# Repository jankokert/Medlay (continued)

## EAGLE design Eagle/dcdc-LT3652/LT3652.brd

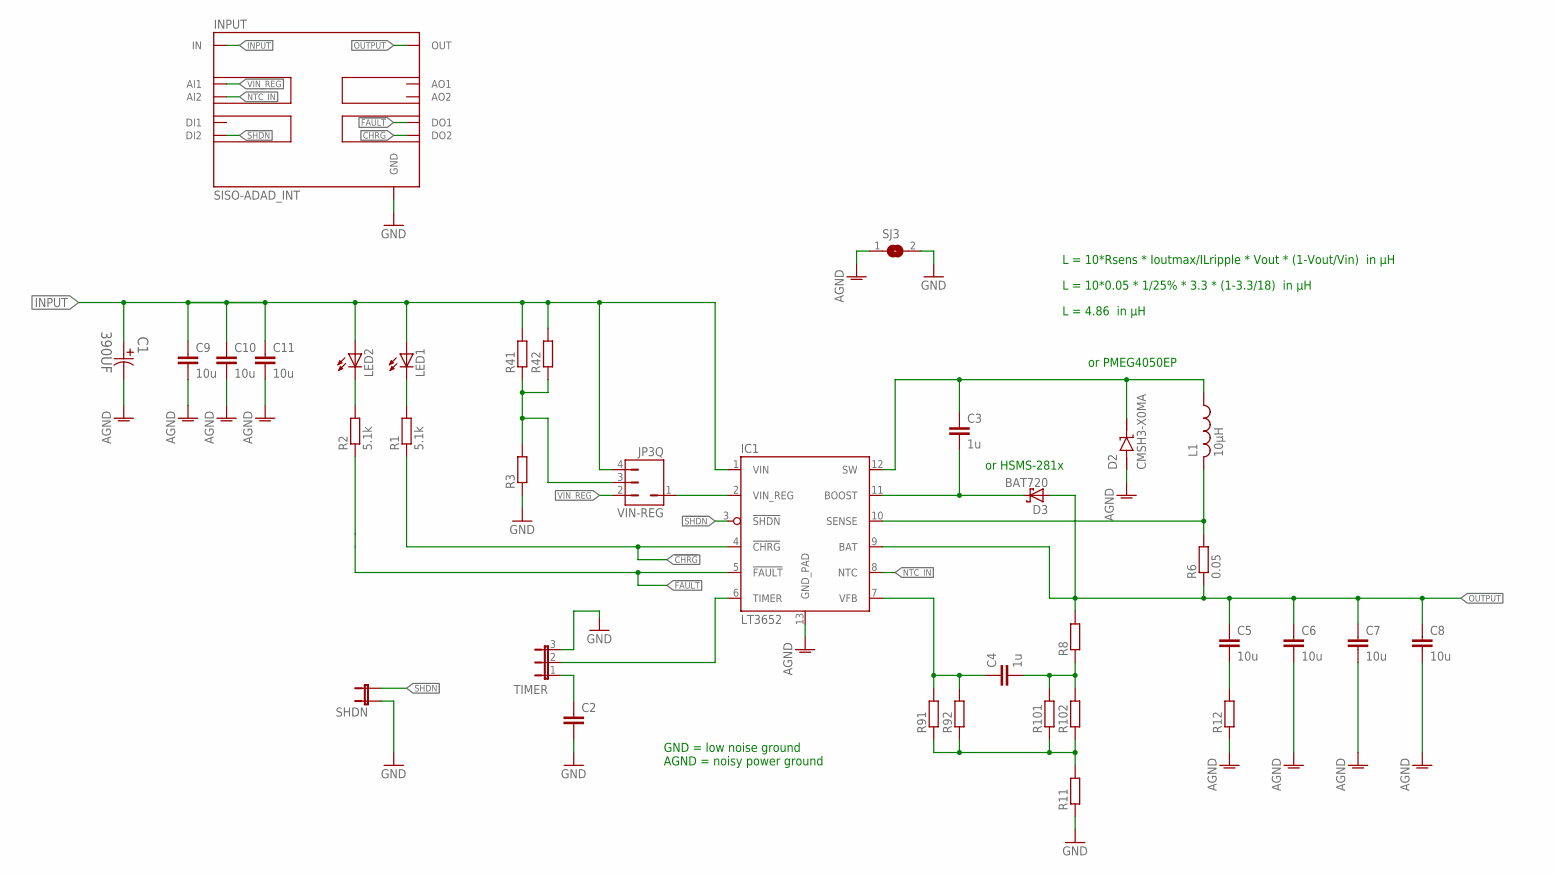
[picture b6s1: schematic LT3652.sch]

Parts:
C1: 390UF; CAPAE1030X1050N
C2: C-EUC0805; C0805
C3, C4: 1u; C0805
C5, C6, C7, C8, C9, C10, C11: 10u; C0805
D2: CMSH3-X0MA; DIODE_SMA
D3: BAT720; SOT23
IC1: LT3652; MSOP-12_GND
INPUT: SISO-ADAD_INT; SISO-ADAD
L1: 10µH; 2525
LED1, LED2: LEDCHIP-LED0805; CHIP-LED0805
R1, R2: 5.1k; R0805
R3, R8, R11, R12, R41, R42, R91, R92, R101, R102: R-EU_R0805; R0805
R6: 0.05; R1206
SHDN: JP2_SMALL_PAD
SJ3: SJ2
TIMER: JP3_SMALL_PAD
VIN-REG: JP3Q; JP1-3

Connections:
!CHRG: IC1.4 (!CHRG), INPUT.DO2, R1.1
!FAULT: IC1.5 (!FAULT), INPUT.DO1, R2.1
!SHDN: IC1.3 (!SHDN), INPUT.DI2, SHDN.2
AGND: C1.2, C6.2, C7.2, C8.2, C9.2, C10.2, C11.2, D2.A, IC1.13 (GND_PAD), R12.1, SJ3.1
D1: LED2.C, R2.2
GND: C2.2, INPUT.GND1 (GND), INPUT.GND2 (GND), INPUT.GND3 (GND), INPUT.GND4 (GND), R3.1, R11.1, SHDN.1, SJ3.2, TIMER.3
INPUT: C1.1, C9.1, C10.1, C11.1, IC1.1 (VIN), INPUT.IN1 (IN), INPUT.IN2 (IN), INPUT.IN3 (IN), INPUT.IN4 (IN), LED1.A, LED2.A, R41.2, R42.2, VIN-REG.4
unnamed: IC1.6 (TIMER), TIMER.2
unnamed: LED1.C, R1.2
unnamed: R3.2, R41.1, R42.1, VIN-REG.3
unnamed: IC1.2 (VIN_REG), VIN-REG.1
unnamed: C3.1, D2.C, IC1.12 (SW), L1.P$2
unnamed: C3.2, D3.3 (C), IC1.11 (BOOST)
unnamed: C2.1, TIMER.1
unnamed: R11.2, R91.1, R92.1, R101.1, R102.1
unnamed: C4.2, R8.1, R101.2, R102.2
unnamed: C5.2, R12.2
unnamed: IC1.10 (SENSE), L1.P$1, R6.2
unnamed: C4.1, IC1.7 (VFB), R91.2, R92.2
NTC_IN: IC1.8 (NTC), INPUT.AI2
OUTPUT: C5.1, C6.1, C7.1, C8.1, D3.1 (A), IC1.9 (BAT), INPUT.OUT1_1 (OUT), INPUT.OUT1_2 (OUT), INPUT.OUT1_3 (OUT), INPUT.OUT1_4 (OUT), R6.1, R8.2
VIN_REG: INPUT.AI1, VIN-REG.2

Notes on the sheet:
or HSMS-281x
GND = low noise ground AGND = noisy power ground
L = 10*Rsens * Ioutmax/ILripple * Vout * (1-Vout/Vin) in µH
L = 10*0.05 * 1/25% * 3.3 * (1-3.3/18) in µH
L = 4.86 in µH
or PMEG4050EP

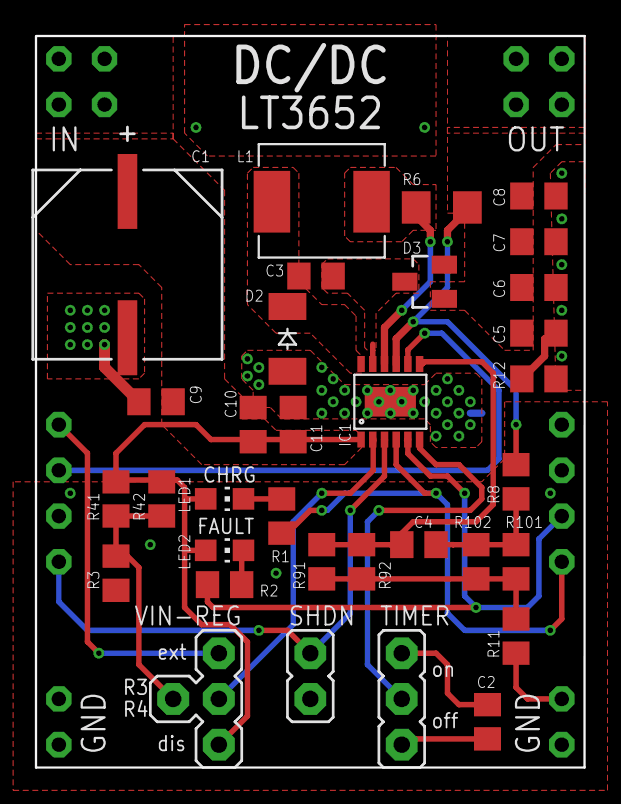
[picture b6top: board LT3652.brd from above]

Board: 2 copper layers, 30.5 x 40.6 mm, 35 parts (1 on the bottom side), 22 nets.

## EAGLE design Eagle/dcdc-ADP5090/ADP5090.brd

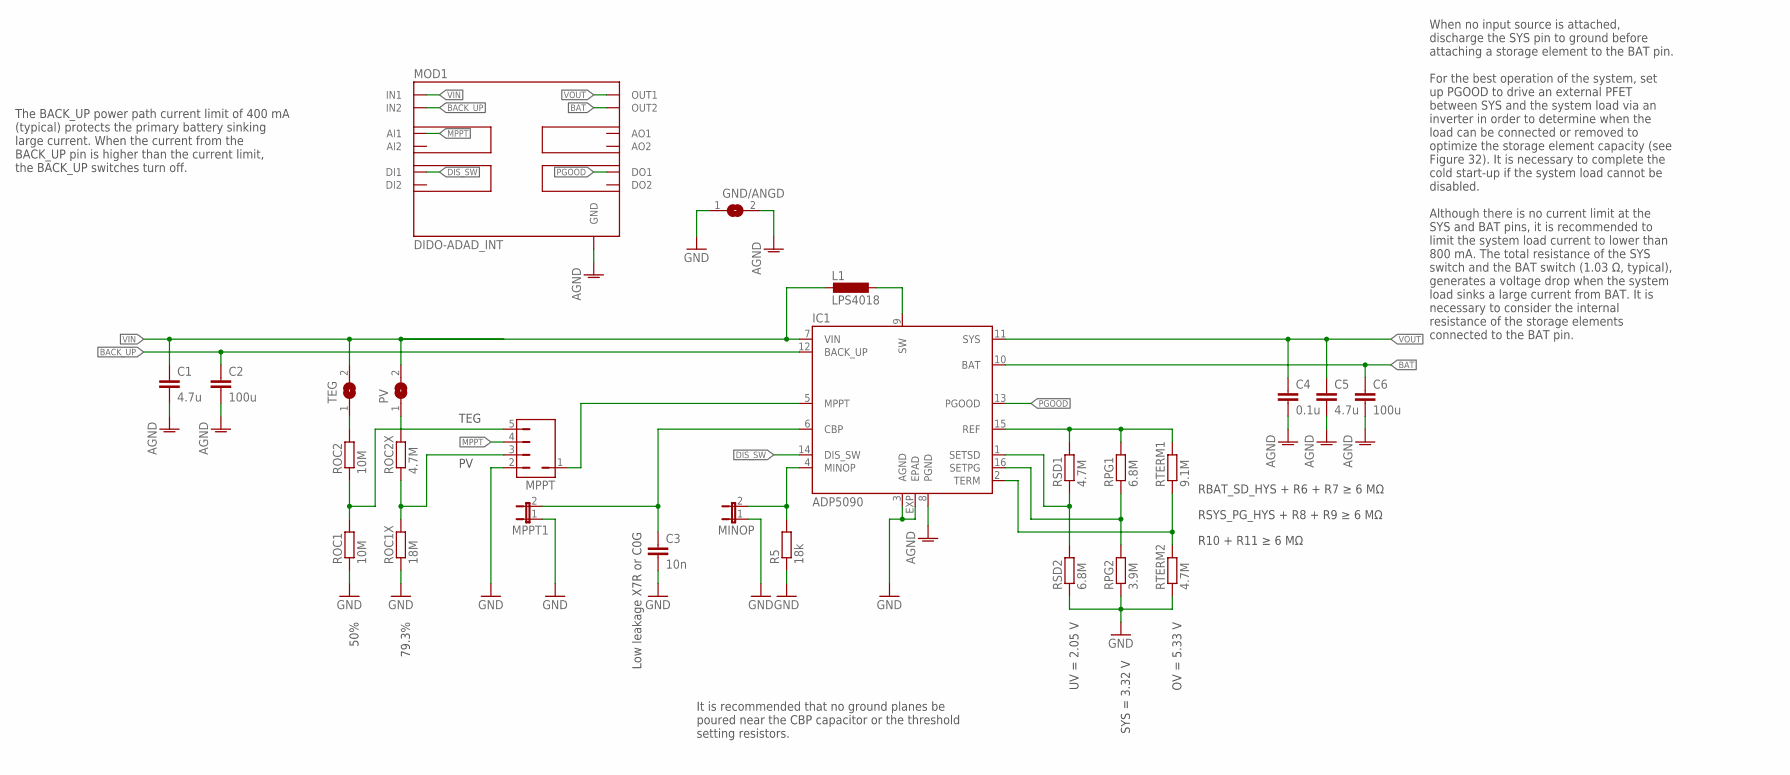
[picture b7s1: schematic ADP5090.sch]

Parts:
C1, C5: 4.7u; C0805
C2, C6: 100u; C0805
C3: 10n; C0805
C4: 0.1u; C0805
GND/ANGD: SJ
IC1: ADP5090; LFCSP16_WQ_CP-16-33
L1: LPS4018
MINOP: JP1E; JP1
MOD1: DIDO-ADAD_INT; DIDO-ADAD
MPPT: JP3Q; JP1-4
MPPT1: JP1E; JP1
PV: SJ
R5: 18k; R0805
ROC1, ROC2: 10M; R0805
ROC1X: 18M; R0805
ROC2X: 4.7M; R0805
RPG1: 6.8M; R0805
RPG2: 3.9M; R0805
RSD1: 4.7M; R0805
RSD2: 6.8M; R0805
RTERM1: 9.1M; R0805
RTERM2: 4.7M; R0805
TEG: SJ

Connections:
AGND: C1.2, C2.2, C4.2, C5.2, C6.2, GND/ANGD.2, IC1.8 (PGND), MOD1.GND1 (GND), MOD1.GND2 (GND), MOD1.GND3 (GND), MOD1.GND4 (GND)
BACK_UP: C2.1, IC1.12 (BACK_UP), MOD1.IN2_1 (IN2), MOD1.IN2_2 (IN2), MOD1.IN2_3 (IN2), MOD1.IN2_4 (IN2)
BAT: C6.1, IC1.10 (BAT), MOD1.OUT2_1 (OUT2), MOD1.OUT2_2 (OUT2), MOD1.OUT2_3 (OUT2), MOD1.OUT2_4 (OUT2)
DIS_SW: IC1.14 (DIS_SW), MOD1.DI1
GND: C3.2, GND/ANGD.1, IC1.3 (AGND), IC1.EXP (EPAD), MINOP.1, MPPT.2, MPPT1.1, R5.1, ROC1.1, ROC1X.1, RPG2.1, RSD2.1, RTERM2.1
MPPT: MOD1.AI1, MPPT.4
unnamed: IC1.15 (REF), RPG1.2, RSD1.2, RTERM1.2
unnamed: IC1.1 (SETSD), RSD1.1, RSD2.2
unnamed: IC1.16 (SETPG), RPG1.1, RPG2.2
unnamed: IC1.2 (TERM), RTERM1.1, RTERM2.2
unnamed: C3.1, IC1.6 (CBP), MPPT1.2
unnamed: MPPT.3, ROC1X.2, ROC2X.1
unnamed: IC1.5 (MPPT), MPPT.1
unnamed: ROC2.2, TEG.1
unnamed: MPPT.5, ROC1.2, ROC2.1
unnamed: PV.1, ROC2X.2
unnamed: IC1.9 (SW), L1.2
unnamed: IC1.4 (MINOP), MINOP.2, R5.2
PGOOD: IC1.13 (PGOOD), MOD1.DO1
VIN: C1.1, IC1.7 (VIN), L1.1, MOD1.IN1_1 (IN1), MOD1.IN1_2 (IN1), MOD1.IN1_3 (IN1), MOD1.IN1_4 (IN1), PV.2, TEG.2
VOUT: C4.1, C5.1, IC1.11 (SYS), MOD1.OUT1_1 (OUT1), MOD1.OUT1_2 (OUT1), MOD1.OUT1_3 (OUT1), MOD1.OUT1_4 (OUT1)

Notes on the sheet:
TEG
When no input source is attached, discharge the SYS pin to ground before attaching a storage element to the BAT pin. For the best operation of the system, set up PGOOD to drive an external PFET between SYS and the system load via an inverter in order to determine when the load can be connected or r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
RSYS_PG_HYS + R8 + R9 ≥ 6 MΩ
RBAT_SD_HYS + R6 + R7 ≥ 6 MΩ
R10 + R11 ≥ 6 MΩ
The BACK_UP power path current limit of 400 mA (typical) protects the primary battery sinking large current. When the current from the BACK_UP pin is higher than the current limit, the BACK_UP switches turn off.
Low leakage X7R or C0G
It is recommended that no ground planes be poured near the CBP capacitor or the threshold setting resistors.
UV = 2.05 V
SYS = 3.32 V
OV = 5.33 V
50%
79.3%

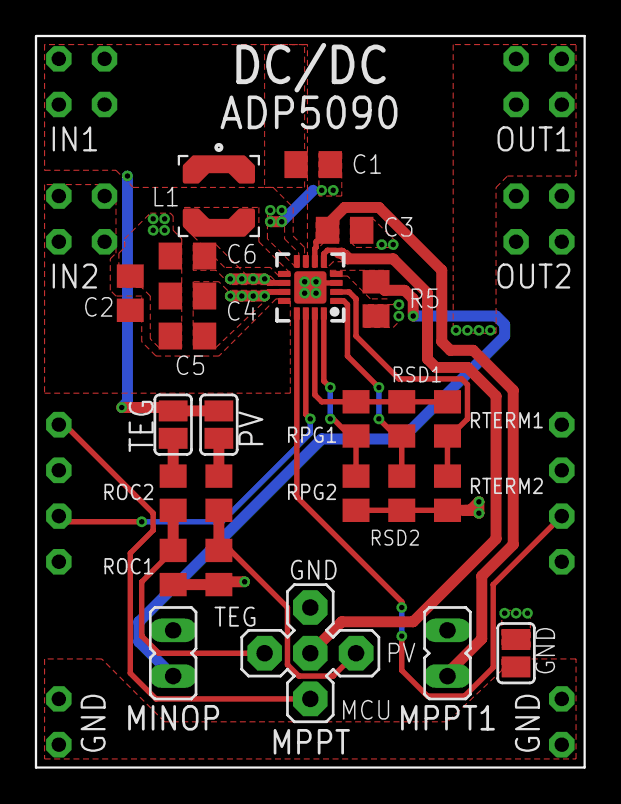
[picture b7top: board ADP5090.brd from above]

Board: 2 copper layers, 30.5 x 40.6 mm, 26 parts (0 on the bottom side), 21 nets.

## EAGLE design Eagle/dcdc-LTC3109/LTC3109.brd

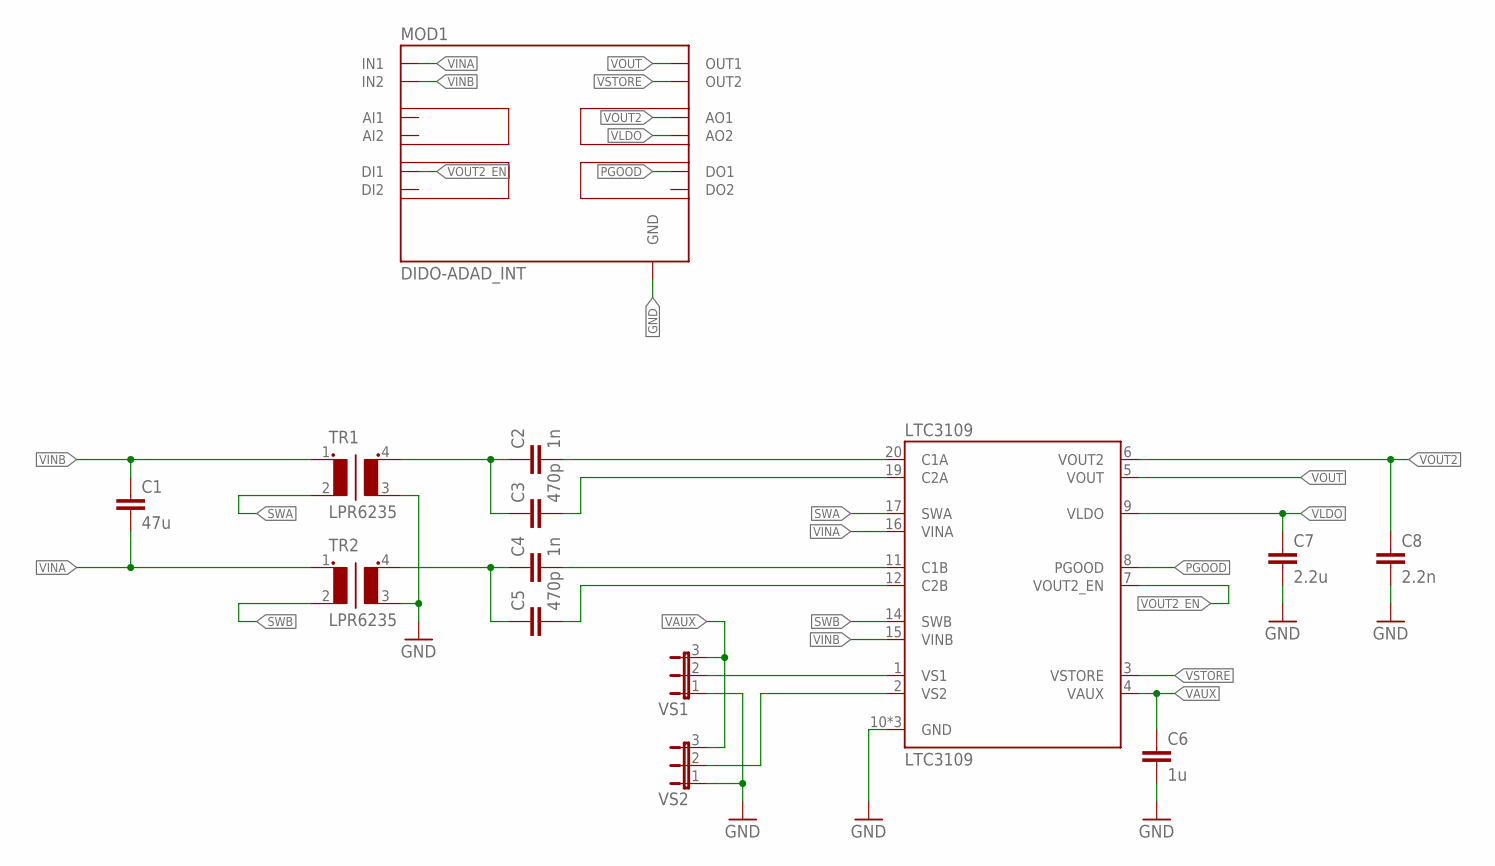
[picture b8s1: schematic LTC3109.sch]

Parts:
C1: 47u; C0805
C2, C4: 1n; C0805
C3, C5: 470p; C0805
C6: 1u; C0805
C7: 2.2u; C0805
C8: 2.2n; C0805
LTC3109: LTC3109; SSOP20_NARROW
MOD1: DIDO-ADAD_INT; DIDO-ADAD
TR1, TR2: LPR6235
VS1, VS2: JP2E; JP2

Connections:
GND: C6.2, C7.2, C8.2, LTC3109.10 (GND), LTC3109.13 (GND), LTC3109.18 (GND), MOD1.GND1 (GND), MOD1.GND2 (GND), MOD1.GND3 (GND), MOD1.GND4 (GND), TR1.3 (S2), TR2.3 (S2), VS1.1, VS2.1
unnamed: C2.2, LTC3109.20 (C1A)
unnamed: C3.2, LTC3109.19 (C2A)
unnamed: C2.1, C3.1, TR1.4 (S1)
unnamed: C4.2, LTC3109.11 (C1B)
unnamed: C5.2, LTC3109.12 (C2B)
unnamed: LTC3109.1 (VS1), VS1.2
unnamed: C4.1, C5.1, TR2.4 (S1)
unnamed: LTC3109.2 (VS2), VS2.2
PGOOD: LTC3109.8 (PGOOD), MOD1.DO1
SWA: LTC3109.17 (SWA), TR1.2
SWB: LTC3109.14 (SWB), TR2.2
VAUX: C6.1, LTC3109.4 (VAUX), VS1.3, VS2.3
VINA: C1.2, LTC3109.16 (VINA), MOD1.IN1_1 (IN1), MOD1.IN1_2 (IN1), MOD1.IN1_3 (IN1), MOD1.IN1_4 (IN1), TR2.1
VINB: C1.1, LTC3109.15 (VINB), MOD1.IN2_1 (IN2), MOD1.IN2_2 (IN2), MOD1.IN2_3 (IN2), MOD1.IN2_4 (IN2), TR1.1
VLDO: C7.1, LTC3109.9 (VLDO), MOD1.AO2
VOUT: LTC3109.5 (VOUT), MOD1.OUT1_1 (OUT1), MOD1.OUT1_2 (OUT1), MOD1.OUT1_3 (OUT1), MOD1.OUT1_4 (OUT1)
VOUT2: C8.1, LTC3109.6 (VOUT2), MOD1.AO1
VOUT2_EN: LTC3109.7 (VOUT2_EN), MOD1.DI1
VSTORE: LTC3109.3 (VSTORE), MOD1.OUT2_1 (OUT2), MOD1.OUT2_2 (OUT2), MOD1.OUT2_3 (OUT2), MOD1.OUT2_4 (OUT2)

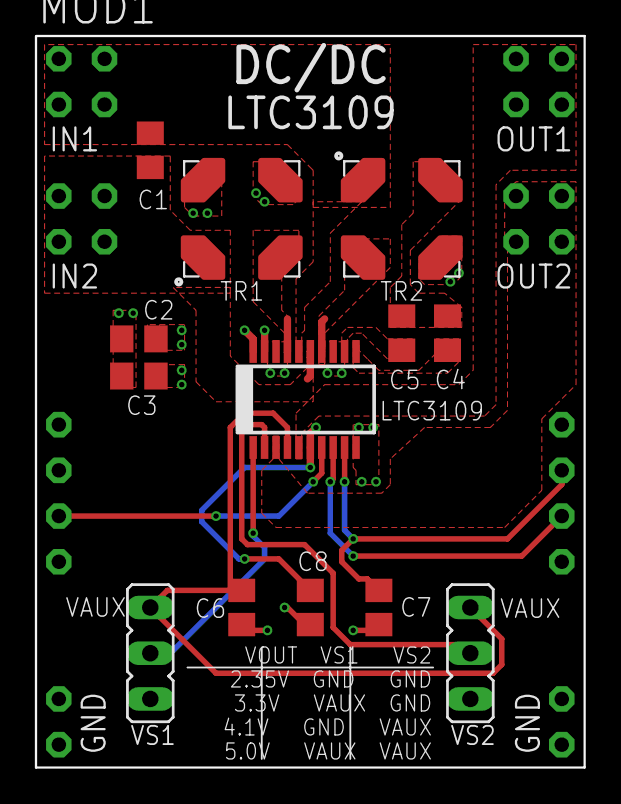
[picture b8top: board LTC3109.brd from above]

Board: 2 copper layers, 30.5 x 40.6 mm, 14 parts (0 on the bottom side), 20 nets.

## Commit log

2017-12-31 Initial commit of Eagle files
    All layouts of Medlay consisting of 24 modules and the base board
2023-12-31 added original supplemental material from MDPI paper
2024-01-02 adjusted layout of replacement rules and exported PDF; restuctured folders; changed start scripts
2024-01-02 renamed jumper rules; graphically moved all edges to the top and aligned nodes perfectly; added pdf exports; added start scripts
